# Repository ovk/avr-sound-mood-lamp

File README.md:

# Summary
This repository contains electronic schematic and firmware for a mood lamp that can react to sound.

For the complete description of the project please see this [blog article](http://null-b.blogspot.ca/2012/06/blog-post.html) (or its [English version by Google Translate](https://translate.google.com/translate?sl=ru&tl=en&js=y&prev=_t&hl=en&ie=UTF-8&u=http%3A%2F%2Fnull-b.blogspot.ca%2F2012%2F06%2Fblog-post.html&edit-text=&act=url)).

# Repository Contents
- `schematic.png`: image with electronic schematic of the device.
- `PCB_600dpi.png`: monochrome image with printed circuit board. It only contains traces and pads so it can be used to manufacture PCB.
- `src`: directory that contains the source code for the firmware.
- `schematic`: directory that contains schematic and PCB projects for Eagle CAD.

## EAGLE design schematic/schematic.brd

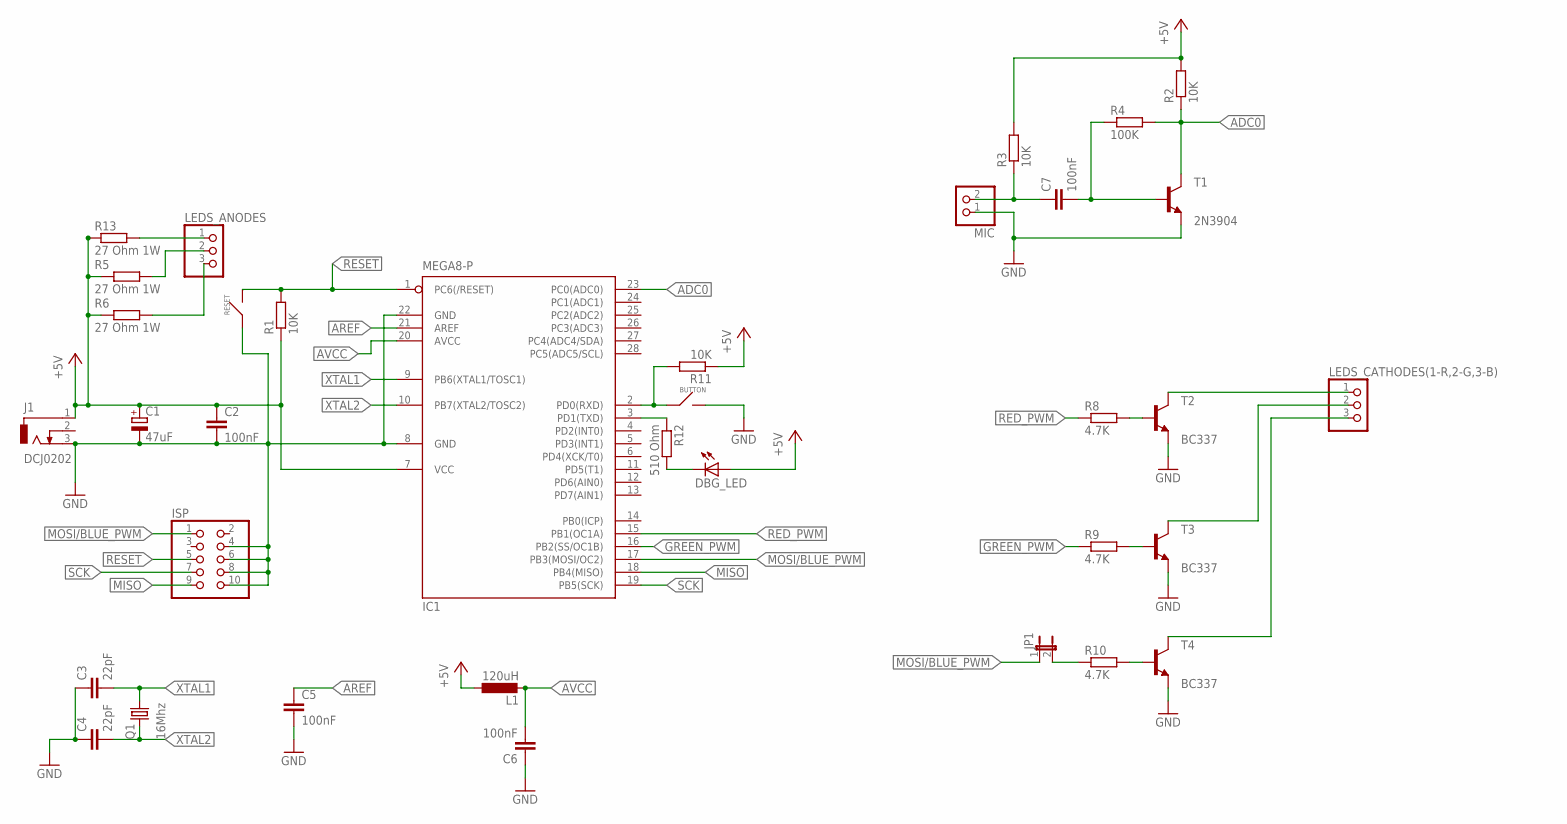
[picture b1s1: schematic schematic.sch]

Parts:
BUTTON: TS1102; TL1105
C1: 47uF; E2-4
C2, C5, C6, C7: 100nF; C1206
C3, C4: 22pF; C050-024X044
DBG_LED: LED3MM
IC1: MEGA8-P; DIL28-3
ISP: PINHD-2X5; 2X05
J1: DCJ0202
JP1: JP1E; JP1
L1: 120uH; 2200-15.24
LEDS_ANODES: PINHD-1X3; 1X03
LEDS_CATHODES(1-R,2-G,3-B): PINHD-1X3; 1X03
MIC: PINHD-1X2; 1X02
Q1: 16Mhz; HC49/S
R1, R2, R3, R11: 10K; M1206
R4: 100K; M0805
R5, R6, R13: 27 Ohm 1W; 0207/12
R8, R9, R10: 4.7K; M0805
R12: 510 Ohm; M1206
RESET: TS1102; TL1105
T1: 2N3904; TO92
T2, T3, T4: BC337; TO92

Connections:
+5V: C1.+, C2.1, DBG_LED.A, IC1.7 (VCC), J1.1, L1.1, R1.1, R2.2, R3.2, R5.1, R6.1, R11.1, R13.1
ADC0: IC1.23 (PC0(ADC0)), R2.1, R4.2, T1.1 (C)
AREF: C5.1, IC1.21 (AREF)
AVCC: C6.2, IC1.20 (AVCC), L1.2
GND: BUTTON.2, C1.-, C2.2, C3.1, C4.1, C5.2, C6.1, IC1.8 (GND), IC1.22 (GND), ISP.4, ISP.6, ISP.8, ISP.10, J1.3, MIC.1, RESET.1, T1.3 (E), T2.1 (E), T3.1 (E), T4.1 (E)
GREEN_PWM: IC1.16 (PB2(SS/OC1B)), R9.1
MISO: IC1.18 (PB4(MISO)), ISP.9
MOSI/BLUE_PWM: IC1.17 (PB3(MOSI/OC2)), ISP.1, JP1.1
unnamed: C7.1, MIC.2, R3.1
unnamed: C7.2, R4.1, T1.2 (B)
unnamed: LEDS_CATHODES(1-R,2-G,3-B).1, T2.3 (C)
unnamed: LEDS_ANODES.1, R13.2
unnamed: LEDS_ANODES.2, R5.2
unnamed: LEDS_ANODES.3, R6.2
unnamed: LEDS_CATHODES(1-R,2-G,3-B).2, T3.3 (C)
unnamed: LEDS_CATHODES(1-R,2-G,3-B).3, T4.3 (C)
unnamed: R8.2, T2.2 (B)
unnamed: R9.2, T3.2 (B)
unnamed: R10.2, T4.2 (B)
unnamed: JP1.2, R10.1
unnamed: BUTTON.1, IC1.2 (PD0(RXD)), R11.2
unnamed: IC1.3 (PD1(TXD)), R12.1
unnamed: DBG_LED.K (C), R12.2
RED_PWM: IC1.15 (PB1(OC1A)), R8.1
RESET: IC1.1 (PC6(/RESET)), ISP.5, R1.2, RESET.2
SCK: IC1.19 (PB5(SCK)), ISP.7
XTAL1: C3.2, IC1.9 (PB6(XTAL1/TOSC1)), Q1.2
XTAL2: C4.2, IC1.10 (PB7(XTAL2/TOSC2)), Q1.1

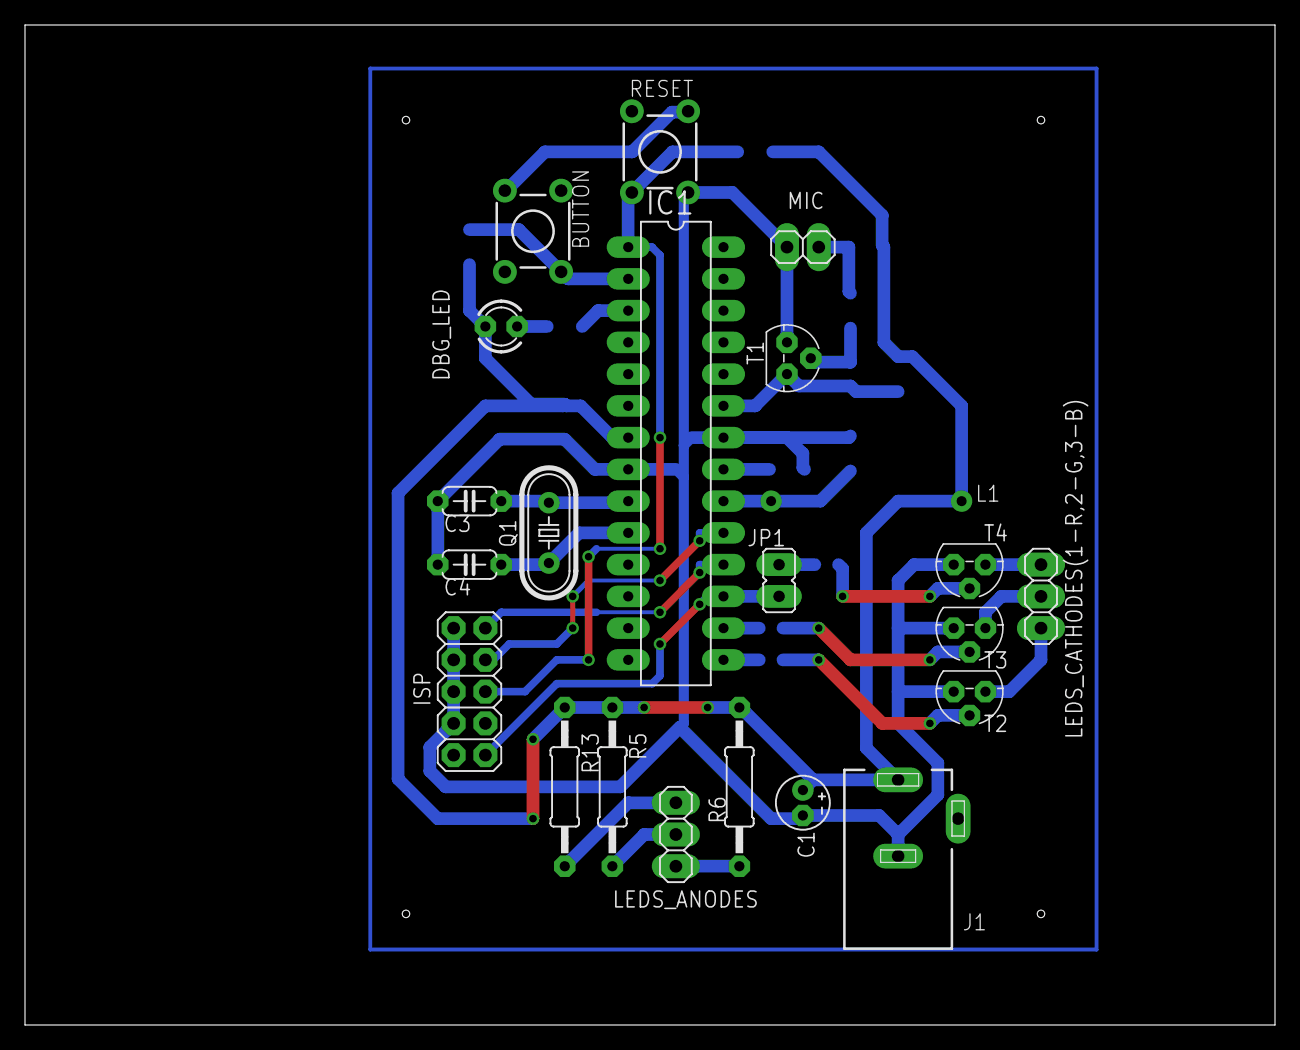
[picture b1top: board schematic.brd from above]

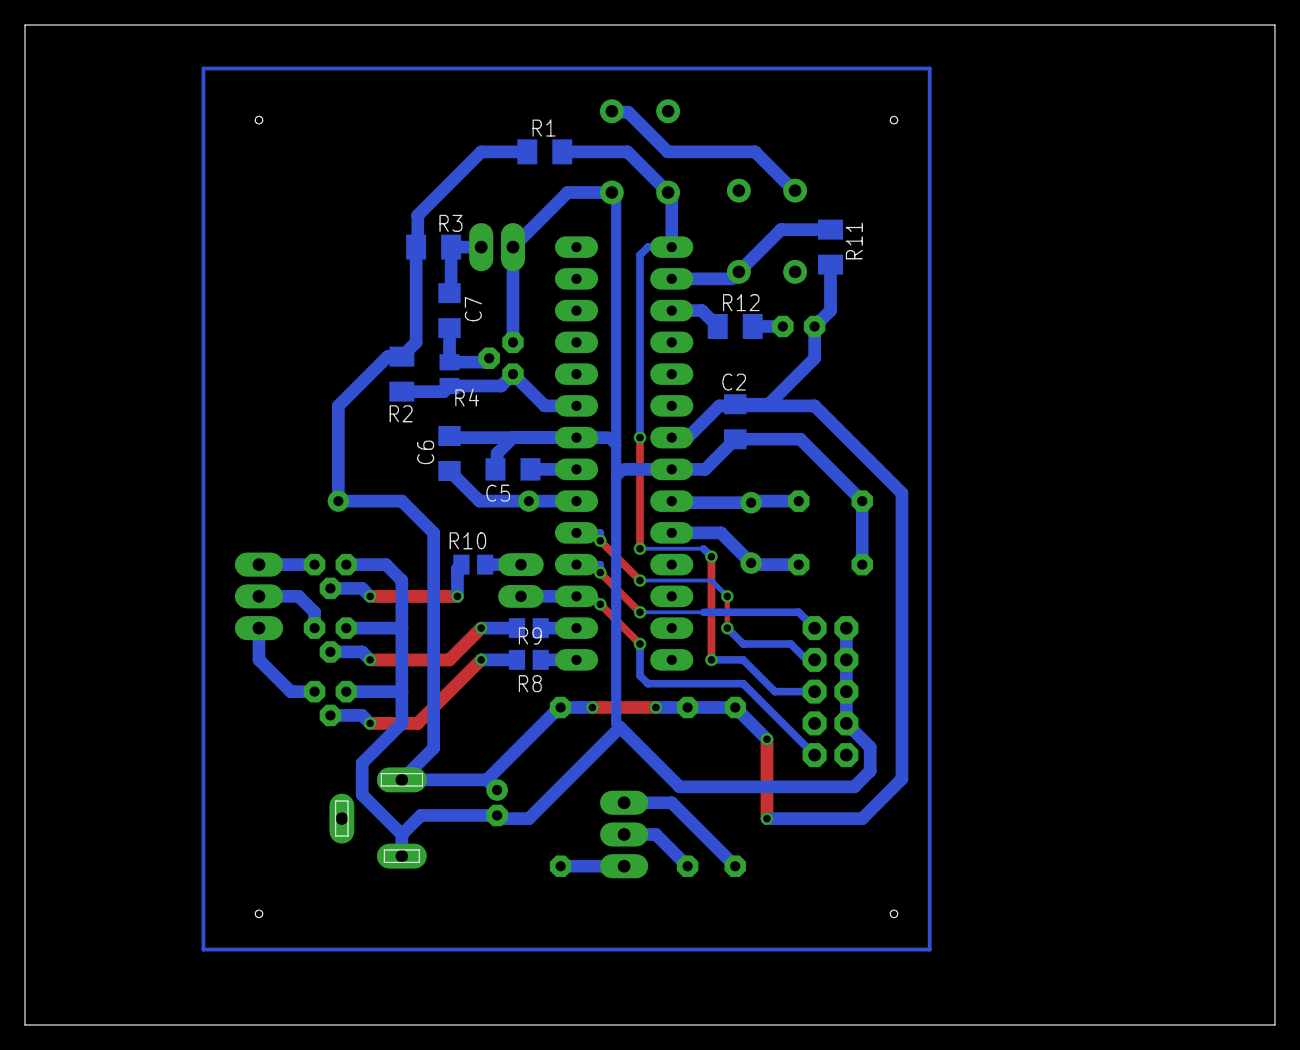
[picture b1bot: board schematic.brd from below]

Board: 2 copper layers, 100.0 x 80.0 mm, 35 parts (13 on the bottom side), 28 nets.

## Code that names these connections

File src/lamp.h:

#ifndef LAMP_H
#define LAMP_H

#define F_CPU 16000000L

#include <avr/io.h>
#include <util/delay.h>
#include <stdlib.h>

/* #define DBG_MODE */

/********** Board-specific parameters ***********/
#define DDR_RED    DDRB
#define DDR_GREEN  DDRB
#define DDR_BLUE   DDRB

#define PORT_RED   PORTB
#define PORT_GREEN PORTB
#define PORT_BLUE  PORTB

#define PIN_RED    (1 << PB1)
#define PIN_GREEN  (1 << PB2)
#define PIN_BLUE   (1 << PB3)

#define TCCR_INIT_RED   { \
                            TCCR1A |= (1 << COM1A1) | (0 << COM1A0) | (0 << WGM11) | (1 << WGM10); \
							TCCR1B |= (0 << WGM13)  | (1 << WGM12)  | (0 << CS12)  | (0 << CS11) | (1 << CS10); \
                        }

#define TCCR_INIT_BLUE  { \
						    TCCR2 |= (1 << WGM20) | (1 << WGM21) | \
							         (1 << COM21) | (0 << COM20) | \
                                     (0 << CS22) | (0 << CS21) | (1 << CS20); \
						}

#define TCCR_INIT_GREEN { \
                            TCCR1A |= (1 << COM1B1) | (0 << COM1B0) | (0 << WGM11) | (1 << WGM10); \
    						TCCR1B |= (0 << WGM13)  | (1 << WGM12)  | (0 << CS12)  | (0 << CS11) | (1 << CS10); \
                        }

#define OCR_RED    OCR1A
#define OCR_GREEN  OCR1B
#define OCR_BLUE   OCR2

#define MIC_ADC_CHANNEL 0

#define DDR_BTN      DDRD
#define PORT_BTN     PORTD
#define PIN_REG_BTN  PIND
#define PIN_BTN      (1 << PD0)

#define DDR_DBG_LED  DDRD
#define PORT_DBG_LED PORTD
#define PIN_DBG_LED  (1 << PD1)

/********** Algorithm configuration parameters ***********/
/* 1-255 */
#define COLOR_MAX	200

/* In percents */
#define COLOR_CLEAR_PROBABILITY 35

/* In milliseconds */
#define MOOD_MODE_COLOR_DELAY         30
#define SOUND_LAMP_MODE_COLOR_DELAY   15

/* In seconds */
#define TIME_TO_HOLD_COLOR 10

/* Loud sound level */
#define LOUD_SOUND 200

/* Number of blinks when switching mode */
#define MODE_SWITCH_BLINKS 5

/* Size of the buffer for sound frequency analysis */
#define SOUND_BUF_SIZE 	128

/* Zero sound amplitude value. Defines which mic level is considered as silence. */
#define SOUND_AMPL_ZERO 100

/**********       Some macros            ***********/
#define SET_RED(value)   OCR_RED   = (value)
#define SET_GREEN(value) OCR_GREEN = (value)
#define SET_BLUE(value)  OCR_BLUE  = (value)

#define BTN_VALUE        ((PIN_REG_BTN & PIN_BTN) ? 0 : 1)

#define DBG_LED_ON       (PORT_DBG_LED &= ~(PIN_DBG_LED))
#define DBG_LED_OFF      (PORT_DBG_LED |=  (PIN_DBG_LED))

/**********       Modes            ***********/
typedef enum
{
	MoodLamp = 0,	/* Simple mood lamp mode */
	SoundLamp,		/* "Change color on loud sound" mode */
	SoundAnalysis,  /* Sound analysis mode */
	ModeLastInvalid
} Mode;

typedef void (*ModeCallback)(void);
typedef void (*ModeSwitchCallback)(void);

#endif /* LAMP_H */

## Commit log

2017-12-25 Add files, update readme
